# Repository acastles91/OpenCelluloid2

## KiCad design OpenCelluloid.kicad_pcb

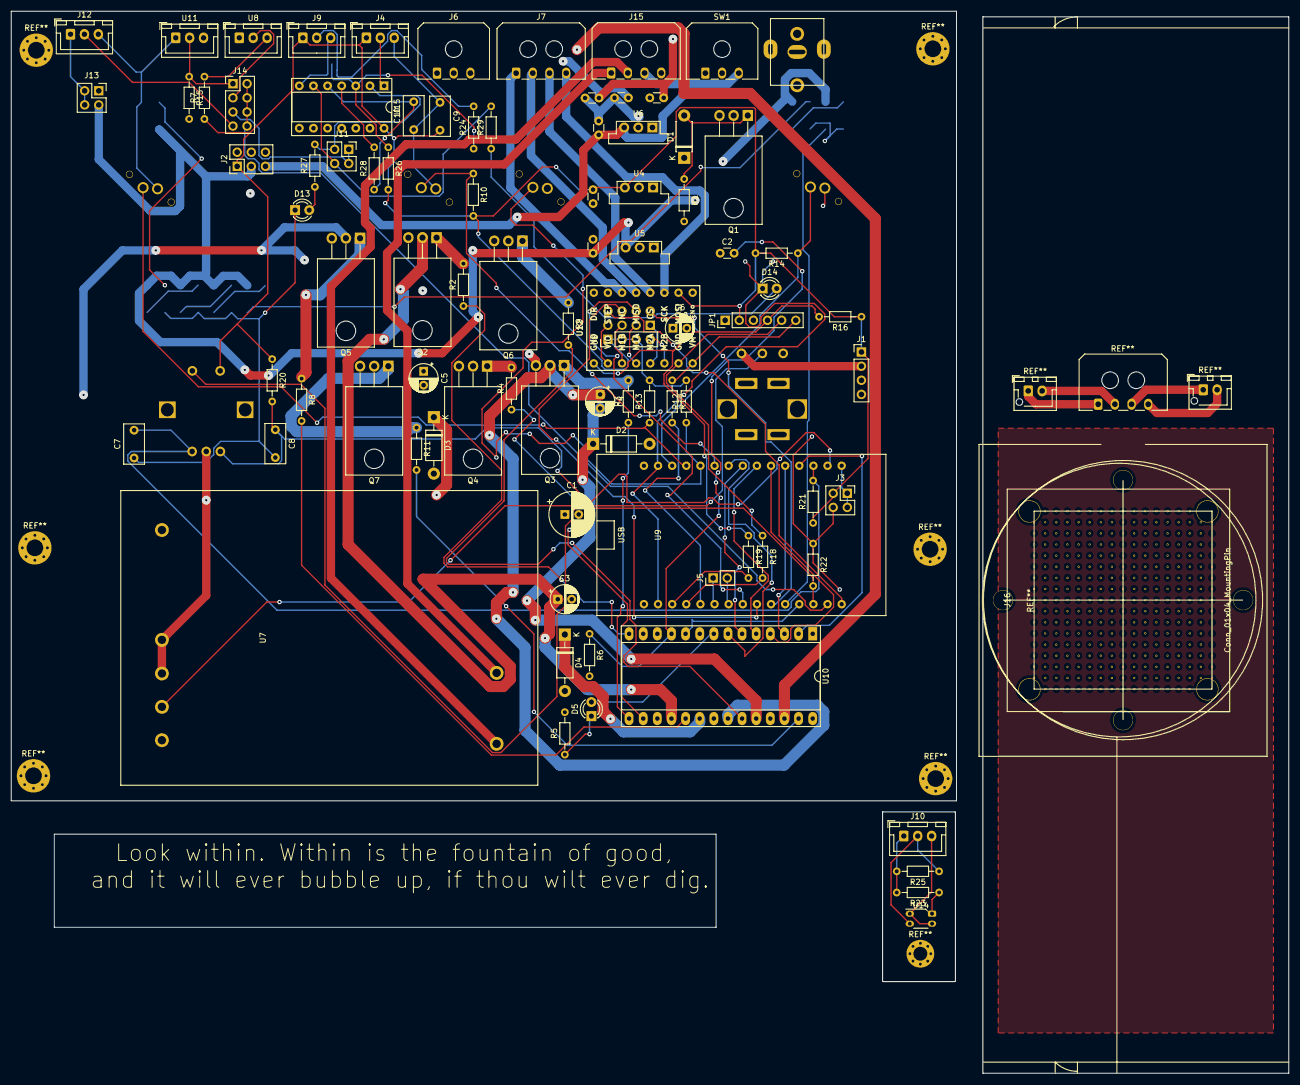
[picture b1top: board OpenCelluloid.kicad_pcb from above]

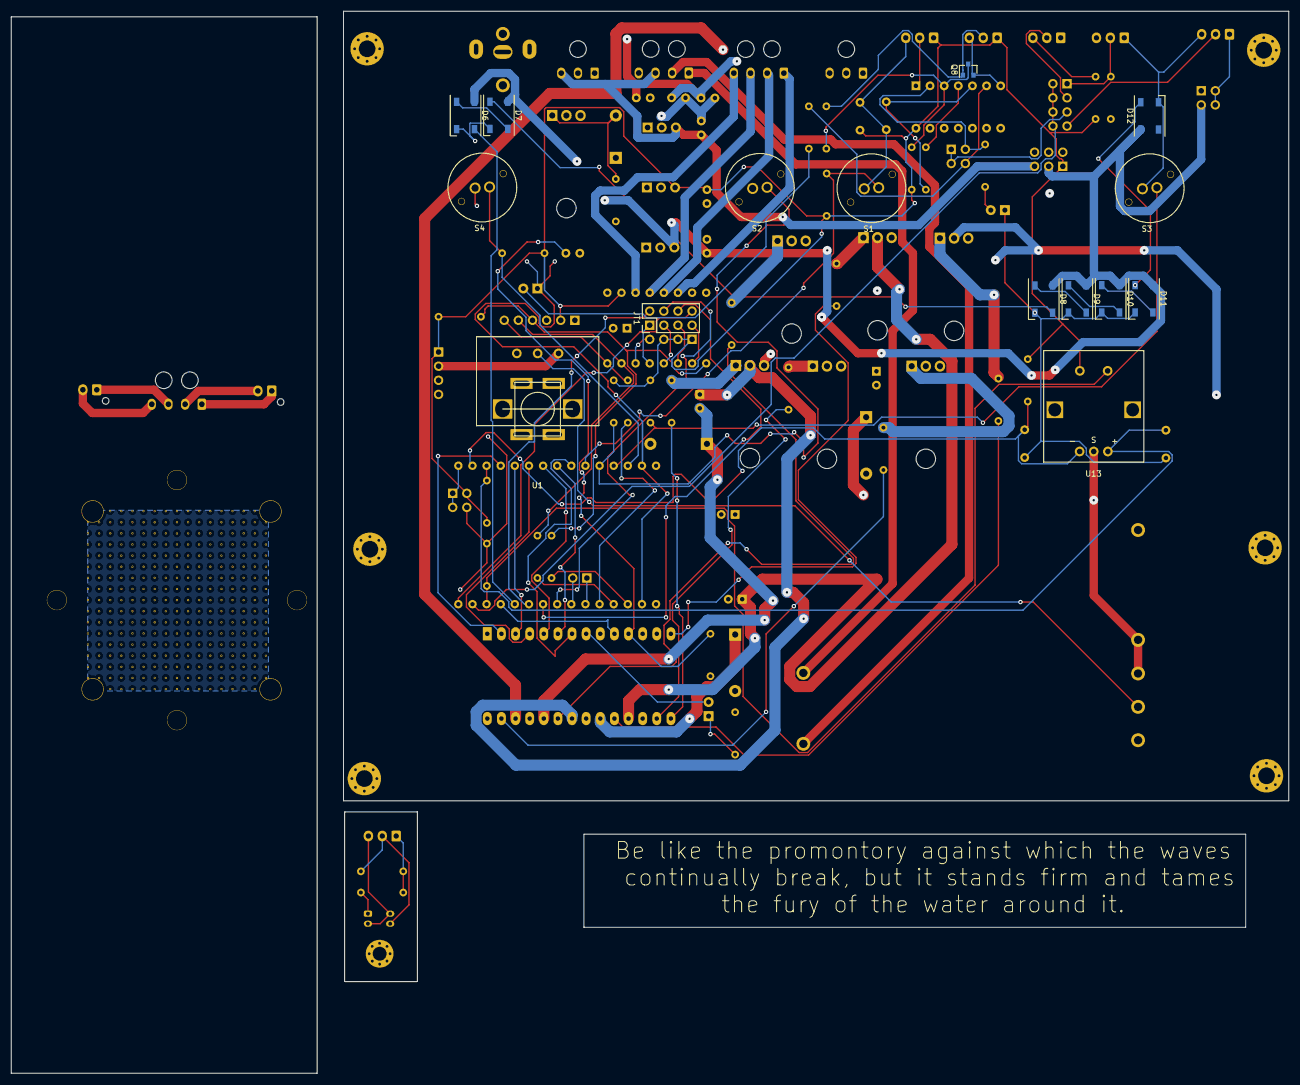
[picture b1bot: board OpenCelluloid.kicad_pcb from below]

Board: 4 copper layers, 229.8 x 191.0 mm, 104 parts (15 on the bottom side), 97 nets.

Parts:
50V-10uF1: C; C_Disc_D3.0mm_W1.6mm_P2.50mm
C1: 100uF 50V; CP_Radial_D8.0mm_P2.50mm
C2: 0.1uF; C_Disc_D3.0mm_W1.6mm_P2.50mm
C3, C4, C5: 10uF 25V; CP_Radial_D5.0mm_P2.50mm
C6: CP1; CP_Radial_D5.0mm_P2.50mm
C7, C8: 0.01uF; C_Rect_L7.0mm_W3.5mm_P5.00mm
C9, C10: C; C_Rect_L7.0mm_W3.5mm_P5.00mm
D1: D_Zener-10V; D_DO-41_SOD81_P7.62mm_Horizontal
D2, D3, D4: 1N4007; D_DO-41_SOD81_P10.16mm_Horizontal
D5, D13, D14: LED; LED_D3.0mm
D6, D7, D8, D9, D10, D11, D12: SK6812; LED_SK6812_PLCC4_5.0x5.0mm_P3.2mm
J1: Conn_01x04_Male; PinHeader_1x04_P2.54mm_Vertical
J2: Conn_02x03_Counter_Clockwise; PinHeader_2x03_P2.54mm_Vertical-CounterClockWise
J3, J11, J13: Conn_02x02_Counter_Clockwise; PinSocket_2x02_P2.54mm_Vertical_CounterClockWise
J4, J9, J10, J12: Conn_01x03_Male; JST_XH_B3B-XH-A_1x03_P2.50mm_Vertical
J5: Conn_01x02_Male; PinHeader_1x02_P2.54mm_Vertical
J6: ConnectorACMotor; Molex_Micro-Fit_3.0_43650-0300_1x03_P3.00mm_Horizontal
J7: ConnectorMotorUpdated; Molex_Micro-Fit_3.0_43650-0400_1x04_P3.00mm_Horizontal
J8: MS; PinHeader_1x04_P2.54mm_Vertical
J14: Conn_02x04_Counter_Clockwise; PinHeader_2x04_P2.54mm_Vertical-CounterClowckWise
J15: Conn_01x04_MountingPin; Molex_Micro-Fit_3.0_43650-0400_1x04_P3.00mm_Horizontal
J16: Conn_01x04_MountingPin; Vero29_w_Fan
JP1: CLS; PinHeader_1x06_P2.54mm_Vertical
JT1: SPI; PinHeader_2x04_P2.54mm_Vertical
Murata-Ceramic-Capacitor-50v1-22uF1, Murata-Ceramic-Capacitor-50v1-22uF2, Murata-Ceramic-Capacitor-50v1-22uF4, Murata-Ceramic-Capacitor-50v1-22uF5, Murata-Ceramic-Capacitor-50v1-22uF6: C; C_Disc_D3.0mm_W1.6mm_P2.50mm
Q1: IRF5305-Reverse-Polarity; TO-220-3_Horizontal_TabDown
Q2, Q3, Q4, Q5, Q6, Q7: IRF540N; TO-220-3_Horizontal_TabDown
Q8: BC847; SOT-23
R1: 100K; R_Axial_DIN0204_L3.6mm_D1.6mm_P7.62mm_Horizontal
R2, R3, R4, R8, R9, R11: 47; R_Axial_DIN0204_L3.6mm_D1.6mm_P7.62mm_Horizontal
R5: 1k; R_Axial_DIN0204_L3.6mm_D1.6mm_P7.62mm_Horizontal
R6: 100k; R_Axial_DIN0204_L3.6mm_D1.6mm_P7.62mm_Horizontal
R7, R16, R17, R18, R19, R23, R24, R25, R26, R27, R28, R29: R; R_Axial_DIN0204_L3.6mm_D1.6mm_P7.62mm_Horizontal
R10, R12, R13, R14, R20, R21, R22: 10K; R_Axial_DIN0204_L3.6mm_D1.6mm_P7.62mm_Horizontal
R15: 330; R_Axial_DIN0204_L3.6mm_D1.6mm_P7.62mm_Horizontal
S1, S2, S3, S4: K12AB-Switch
SW1: powerButtonConnector; Molex_Micro-Fit_3.0_43650-0300_1x03_P3.00mm_Horizontal
U1: POTENTIOMETER-OpenSourceCelluloid; PDB12-H4301-Potentiometer
U2: POWER_CONNECTOR-DCJ250-20-B-K1-A; POWER_JACK_DCJ250-20-B-K1-A
U4: OKI-78SR-3.3v; Converter_DCDC_muRata_OKI-78SR_Vertical
U5: OKI-78SR-5v; Converter_DCDC_muRata_OKI-78SR_Vertical
U6: OKI-78SR-12v; Converter_DCDC_muRata_OKI-78SR_Vertical
U7: LDH-45B-1050; MeanWell-LDH-45B-1050
U8, U11: Connector-Sensor; JST_XH_B3B-XH-A_1x03_P2.50mm_Vertical
U9: ESP32-WROOM-32D; ESP32-DEVKIT
U10: IR2136; DIP-28_W15.24mm_Socket_LongPads
U12: stepStick; STEPSTICK
U13: PEC12R-ENCODER; PEC12R-Encoder
U14: QRE1113; OnSemi_CASE100AQ
U15: 74HC14; DIP-14_W7.62mm_Socket

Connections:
45B_OUT+: J15.1, U7.7
45B_OUT-: J15.2, U7.6
+3V3: C9.2, J1.1, J2.1, J3.1, J4.1, J8.1, J8.2, J8.3, J9.1, J13.4, JP1.2, Murata-Ceramic-Capacitor-50v1-22uF4.1, R7.1, R10.2, R12.2, R13.2, R14.2, R15.2, R16.1, R20.1, R21.1, R26.2, U4.3, U12.10, U13.4, U15.14
+5V: D6.3, D7.3, D8.3, D9.3, D10.3, D11.3, D12.3, J1.2, J2.2, J13.3, Murata-Ceramic-Capacitor-50v1-22uF5.1, U1.1, U5.3, U9.15
+12V: J1.3, J2.3, J15.3, Murata-Ceramic-Capacitor-50v1-22uF6.1, SW1.3, U6.3
+24V: 50V-10uF1.1, C6.1, D1.1, Murata-Ceramic-Capacitor-50v1-22uF1.1, Murata-Ceramic-Capacitor-50v1-22uF2.1, Q1.3, Q5.2, Q6.2, Q7.2, U4.1, U5.1, U6.1, U7.1, U12.16
CAPTURE: R13.1, S3.1, U9.12
DIR: JP1.6, R17.1, U12.8
DIRSWITCH: R10.1, S1.1, U9.10
EN: JP1.4, R16.2, R19.1, U12.1
EN2: U9.27, U10.10
GND: 50V-10uF1.2, C1.1, C2.1, C6.2, J1.4, J15.4, JP1.3, Murata-Ceramic-Capacitor-50v1-22uF1.2, Murata-Ceramic-Capacitor-50v1-22uF2.2, Murata-Ceramic-Capacitor-50v1-22uF4.2, Murata-Ceramic-Capacitor-50v1-22uF5.2, Murata-Ceramic-Capacitor-50v1-22uF6.2, Q2.3, Q3.3, Q4.3, R1.2, U1.3, U2.2, U4.2, U5.2, U6.2, U7.2, U7.3, U10.9, U10.12, U10.13, U12.9, U12.15, U13.2
GNDD: C7.1, C8.2, C9.1, C10.1, D6.1, D7.1, D8.1, D9.1, D10.1, D11.1, D12.1, D13.1, D14.1, J3.2, J4.3, J9.3, J12.3, Q8.2, R22.1, S1.2, S2.2, S3.2, S4.2, U8.1, U9.14, U9.17, U11.1, U15.7
HIN1: U9.4, U10.2
HIN2: U9.5, U10.3
HIN3: U9.6, U10.4
LEDS: D6.2, U9.26
LIN1: U9.7, U10.5
LIN2: U9.8, U10.6
LIN3: U9.9, U10.7
MODE: R14.1, S4.1, U9.13
unnamed: C1.2, D2.2, D3.2, D4.2, J2.4, J2.5, J2.6, R5.2, R6.2, U10.1
unnamed: C2.2, R6.1, U10.11
unnamed: C3.2, D4.1, U10.20
unnamed: C4.2, D2.1, U10.24
unnamed: C5.2, D3.1, U10.28
unnamed: C10.2, R28.1, U15.5
unnamed: D1.2, Q1.1, R1.1
unnamed: D5.1, R5.1
unnamed: D5.2, U10.8
unnamed: D6.4, D7.2
unnamed: D7.4, D8.2
unnamed: D8.4, D9.2
unnamed: D9.4, D10.2
unnamed: D10.4, D11.2
unnamed: D11.4, D12.2
unnamed: D13.2, R27.1
unnamed: D14.2, R29.1
unnamed: J3.3, J3.4, U9.1
unnamed: J4.2, U15.1
unnamed: J5.1, U9.21
unnamed: J5.2, U9.22
unnamed: J7.1, U12.14
unnamed: J7.2, U12.13
unnamed: J7.3, U12.12
unnamed: J7.4, U12.11
unnamed: J9.2, Q8.1, R24.2
unnamed: J11.1, R27.2, U15.2
unnamed: J11.2, R29.2, U15.6
unnamed: J12.1, J13.1, J13.2
unnamed: JT1.1, U12.5
unnamed: JT1.3, U12.4
unnamed: JT1.5, U12.3
unnamed: JT1.7, U12.2
unnamed: Q1.2, SW1.1
unnamed: Q2.1, R2.2
unnamed: Q3.1, R3.2
unnamed: Q4.1, R4.2
unnamed: Q5.1, R8.1
unnamed: Q6.1, R9.1
unnamed: Q7.1, R11.1
unnamed: Q8.3, R24.1, R26.1, U15.3
unnamed: R2.1, U10.14
unnamed: R3.1, U10.15
unnamed: R4.1, U10.16
unnamed: R7.2, U8.3
unnamed: R8.2, U10.19
unnamed: R9.2, U10.23
unnamed: R11.2, U10.27
unnamed: R23.1, U14.1
unnamed: R28.2, U15.4
unnamed: SW1.2, U2.1
unnamed: U1.2, U7.4
SENSOR+: J10.1, R23.2, R25.2
SENSOR-: J10.3, U14.2, U14.4
SENSOR-CRASS: J14.1, R15.1, U11.2
SENSOR-SIGNAL: J10.2, R25.1, U14.3
SENSOR-SIMPLE: J14.2, U8.2
SENSOR-SYNKINO: J11.3, J11.4, J14.3
SLP: J8.4, U12.6
STARTSTOP: R12.1, S2.1, U9.11
STP: JP1.5, R18.1, U12.7
_CHANNEL-A: C7.2, R21.2, U9.3, U13.1
_CHANNEL-B: C8.1, R20.2, U9.2, U13.3
_DIR: R17.2, U9.20
_EN: R19.2, U9.18
_ENCO-BUTTON: R22.2, U9.28, U13.5
_MISO: JT1.2, U9.25
_MOSI: JT1.8, U9.30
_RX: JT1.4, U9.23
_SCK: JT1.6, U9.24
_SENSOR: J14.5, J14.6, J14.7, J14.8, U9.29
_SENSOR-SIGNAL: J12.2, J14.4
_STP: R18.2, U9.19
coilA: C5.1, J6.1, Q4.2, Q7.3, U10.26
coilB: C4.1, J6.2, Q3.2, Q6.3, U10.22
coilC: C3.1, J6.3, Q2.2, Q5.3, U10.18

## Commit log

2021-04-29 29.04
2021-06-12 After pcb production
2021-06-25 tabla precios
